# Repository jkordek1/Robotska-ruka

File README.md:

# Robotska-ruka
## What is it?
Board used for controlling multiple servo motors and their measurement of current.

WiFI capability via ESP32.

## Project status
Development stopped.

## Images

## Project folder structure
    .
    ├── ...
    ├── Images                  # Project images folder
    ├── Output files            # Gerber files folder
    ├── KiCad files             # Main folder
    ├── Schematic.pdf           # Schematic in .pdf format
    └── ...

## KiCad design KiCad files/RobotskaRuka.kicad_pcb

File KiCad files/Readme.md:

Board used for controlling multiple servo motors and current measurement of each motor.

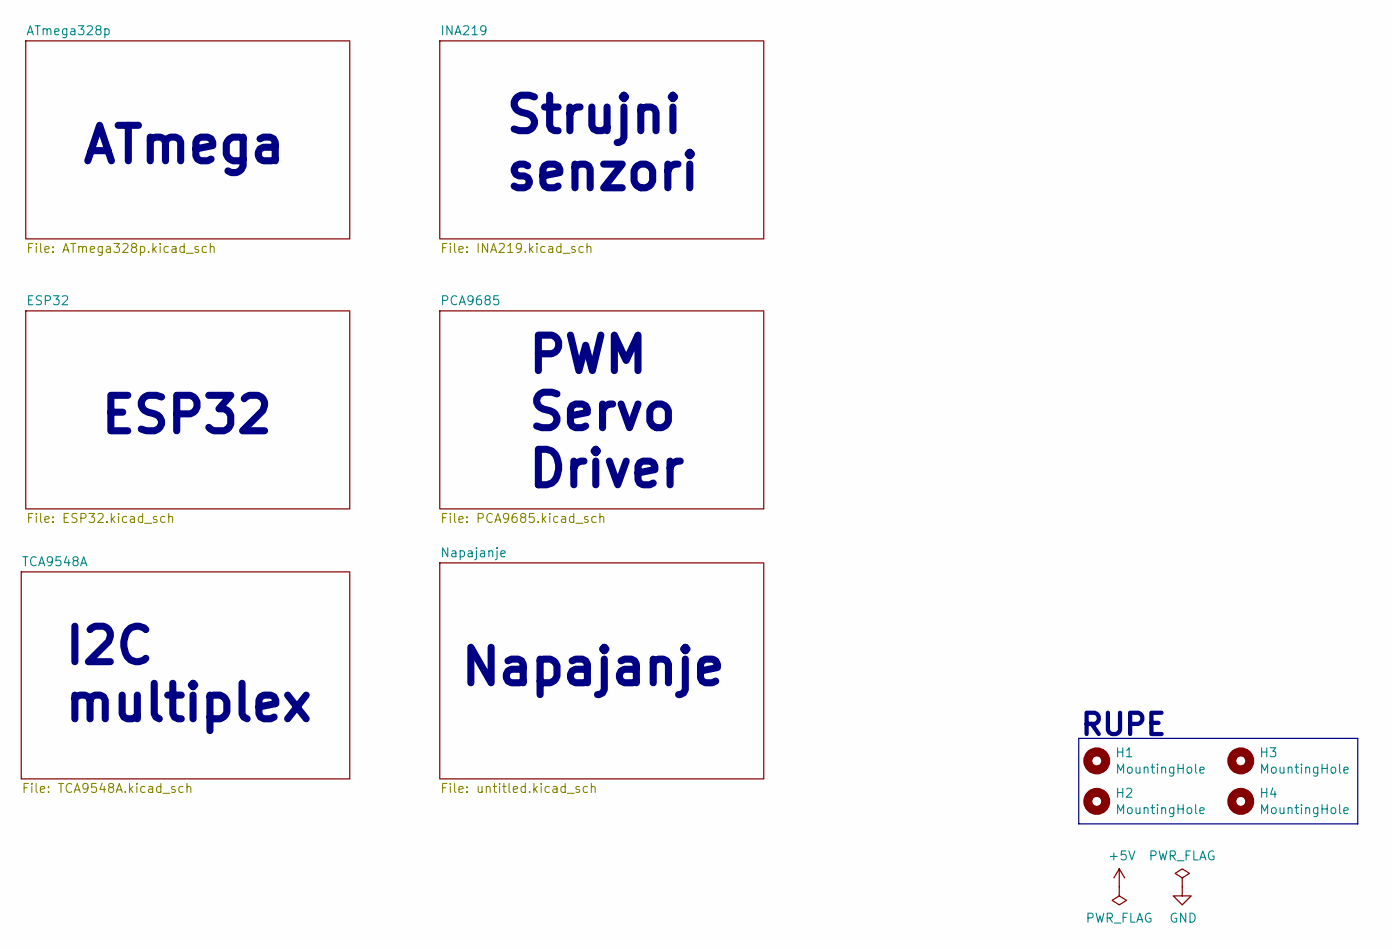
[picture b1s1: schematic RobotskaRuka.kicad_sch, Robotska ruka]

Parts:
H1, H2, H3, H4: MountingHole; MountingHole_3.2mm_M3_Pad_Via

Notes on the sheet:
ESP32
RUPE
Strujni senzori
PWM Servo Driver
Napajanje
ATmega
I2C multiplex

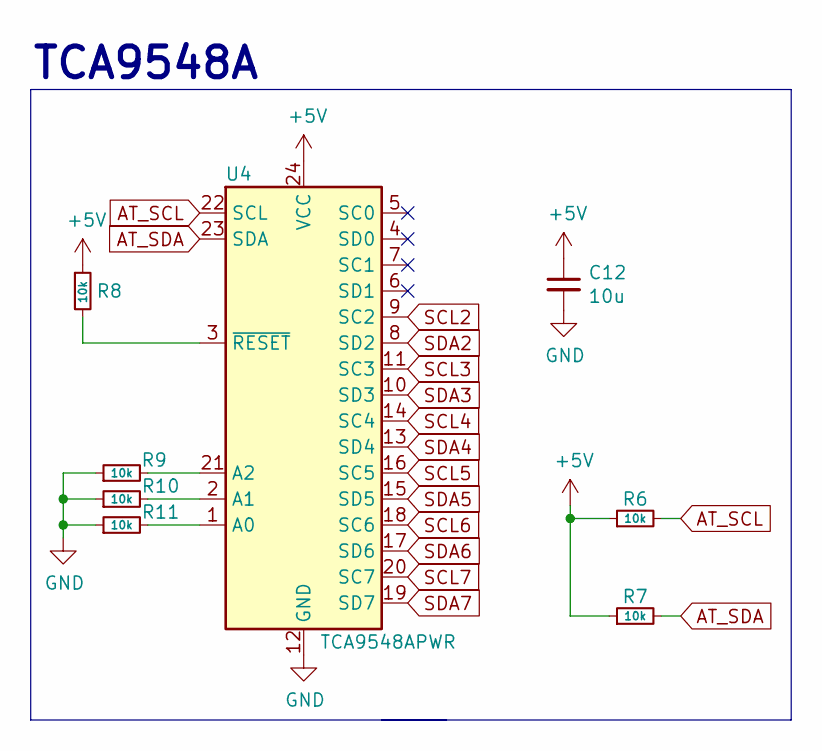
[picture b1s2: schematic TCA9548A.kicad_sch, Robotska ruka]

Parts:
C12: 10u; C_0805_2012Metric
R6, R7, R8, R9, R10, R11: 10k; R_0805_2012Metric
U4: TCA9548APWR; TSSOP-24_4.4x7.8mm_P0.65mm

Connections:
+5V: C12.1, R6.1, R7.1, R8.1, U4.24 (VCC); also elsewhere on the board
AT_SCL: R6.2, U4.22 (SCL); also elsewhere on the board
AT_SDA: R7.2, U4.23 (SDA); also elsewhere on the board
GND: C12.2, R9.1, R10.1, R11.1, U4.12 (GND); also elsewhere on the board
unnamed: R8.2, U4.3 (~RESET)
unnamed: R9.2, U4.21 (A2)
unnamed: R10.2, U4.2 (A1)
unnamed: R11.2, U4.1 (A0)
SCL1: U4.7 (SC1)
SCL2: U4.9 (SC2); also elsewhere on the board
SCL3: U4.11 (SC3); also elsewhere on the board
SCL4: U4.14 (SC4); also elsewhere on the board
SCL5: U4.16 (SC5); also elsewhere on the board
SCL6: U4.18 (SC6); also elsewhere on the board
SCL7: U4.20 (SC7); also elsewhere on the board
SDA1: U4.6 (SD1)
SDA2: U4.8 (SD2); also elsewhere on the board
SDA3: U4.10 (SD3); also elsewhere on the board
SDA4: U4.13 (SD4); also elsewhere on the board
SDA5: U4.15 (SD5); also elsewhere on the board
SDA6: U4.17 (SD6); also elsewhere on the board
SDA7: U4.19 (SD7); also elsewhere on the board

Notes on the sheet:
TCA9548A

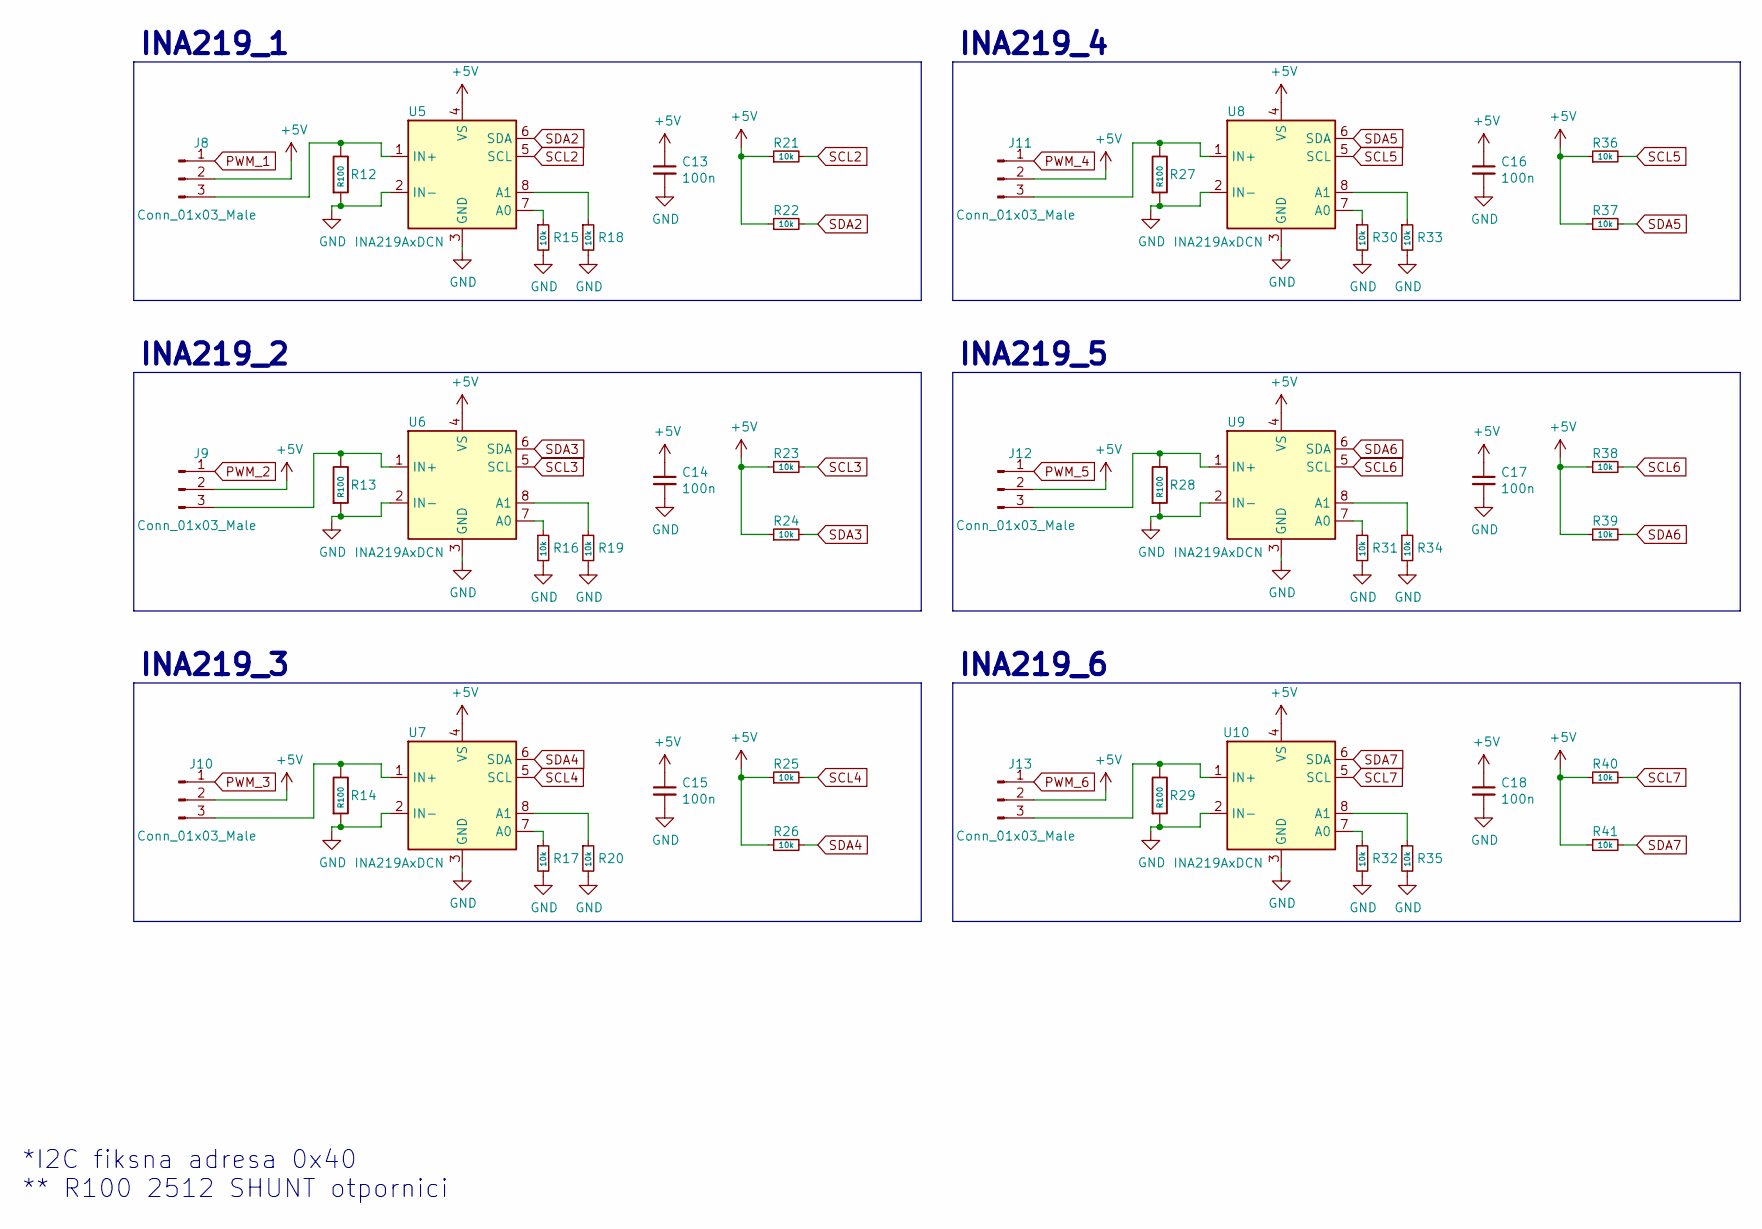
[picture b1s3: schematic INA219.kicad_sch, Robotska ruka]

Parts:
C13, C14, C15, C16, C17, C18: 100n; C_0805_2012Metric
J8, J9, J10, J11, J12, J13: Conn_01x03_Male; PinHeader_1x03_P2.54mm_Horizontal
R12, R13, R14, R27, R28, R29: R100; R_2512_6332Metric
R15, R16, R17, R18, R19, R20, R21, R22, R23, R24, R25, R26, R30, R31, R32, R33, R34, R35, R36, R37, R38, R39, R40, R41: 10k; R_0805_2012Metric
U5, U6, U7, U8, U9, U10: INA219AxDCN; SOT-23-8

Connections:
+5V: C13.1, C14.1, C15.1, C16.1, C17.1, C18.1, J8.2, J9.2, J10.2, J11.2, J12.2, J13.2, R21.1, R22.1, R23.1, R24.1, R25.1, R26.1, R36.1, R37.1, R38.1, R39.1, R40.1, R41.1, U5.4 (VS), U6.4 (VS), U7.4 (VS), U8.4 (VS), U9.4 (VS), U10.4 (VS); also elsewhere on the board
GND: C13.2, C14.2, C15.2, C16.2, C17.2, C18.2, R12.2, R13.2, R14.2, R15.2, R16.2, R17.2, R18.2, R19.2, R20.2, R27.2, R28.2, R29.2, R30.2, R31.2, R32.2, R33.2, R34.2, R35.2, U5.2 (IN-), U5.3 (GND), U6.2 (IN-), U6.3 (GND), U7.2 (IN-), U7.3 (GND), U8.2 (IN-), U8.3 (GND), U9.2 (IN-), U9.3 (GND), U10.2 (IN-), U10.3 (GND); also elsewhere on the board
unnamed: J8.3, R12.1, U5.1 (IN+)
unnamed: J9.3, R13.1, U6.1 (IN+)
unnamed: J10.3, R14.1, U7.1 (IN+)
unnamed: J11.3, R27.1, U8.1 (IN+)
unnamed: J12.3, R28.1, U9.1 (IN+)
unnamed: J13.3, R29.1, U10.1 (IN+)
unnamed: R15.1, U5.7 (A0)
unnamed: R16.1, U6.7 (A0)
unnamed: R17.1, U7.7 (A0)
unnamed: R18.1, U5.8 (A1)
unnamed: R19.1, U6.8 (A1)
unnamed: R20.1, U7.8 (A1)
unnamed: R30.1, U8.7 (A0)
unnamed: R31.1, U9.7 (A0)
unnamed: R32.1, U10.7 (A0)
unnamed: R33.1, U8.8 (A1)
unnamed: R34.1, U9.8 (A1)
unnamed: R35.1, U10.8 (A1)
PWM_1: J8.1; also elsewhere on the board
PWM_2: J9.1; also elsewhere on the board
PWM_3: J10.1; also elsewhere on the board
PWM_4: J11.1; also elsewhere on the board
PWM_5: J12.1; also elsewhere on the board
PWM_6: J13.1; also elsewhere on the board
SCL2: R21.2, U5.5 (SCL); also elsewhere on the board
SCL3: R23.2, U6.5 (SCL); also elsewhere on the board
SCL4: R25.2, U7.5 (SCL); also elsewhere on the board
SCL5: R36.2, U8.5 (SCL); also elsewhere on the board
SCL6: R38.2, U9.5 (SCL); also elsewhere on the board
SCL7: R40.2, U10.5 (SCL); also elsewhere on the board
SDA2: R22.2, U5.6 (SDA); also elsewhere on the board
SDA3: R24.2, U6.6 (SDA); also elsewhere on the board
SDA4: R26.2, U7.6 (SDA); also elsewhere on the board
SDA5: R37.2, U8.6 (SDA); also elsewhere on the board
SDA6: R39.2, U9.6 (SDA); also elsewhere on the board
SDA7: R41.2, U10.6 (SDA); also elsewhere on the board

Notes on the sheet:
INA219_1
INA219_5
*I2C fiksna adresa 0x40 ** R100 2512 SHUNT otpornici
INA219_2
INA219_6
INA219_4
INA219_3

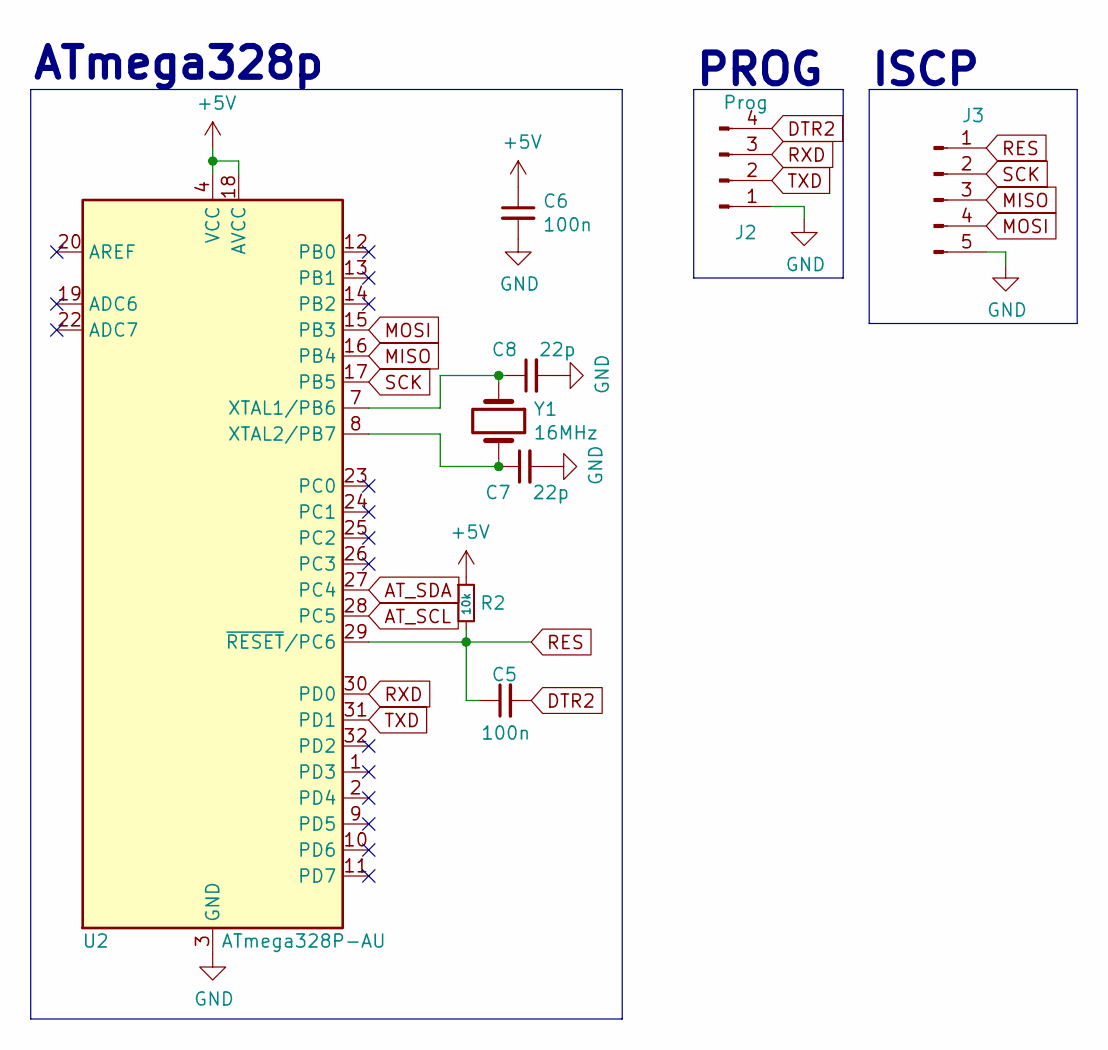
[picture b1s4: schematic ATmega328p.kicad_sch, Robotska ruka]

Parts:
C5, C6: 100n; C_0805_2012Metric
C7, C8: 22p; C_0805_2012Metric
J2: Prog; PinHeader_1x04_P2.54mm_Horizontal
J3: Conn_01x05_Male; PinHeader_1x05_P2.54mm_Horizontal
R2: 10k; R_0805_2012Metric
U2: ATmega328P-AU; TQFP-32_7x7mm_P0.8mm
Y1: 16MHz; Crystal_HC49-4H_Vertical

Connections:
+5V: C6.1, R2.1, U2.4 (VCC), U2.6 (VCC), U2.18 (AVCC); also elsewhere on the board
AT_SCL: U2.28 (PC5); also elsewhere on the board
AT_SDA: U2.27 (PC4); also elsewhere on the board
DTR2: C5.2, J2.4
GND: C6.2, C7.2, C8.2, J2.1, J3.5, U2.3 (GND), U2.5 (GND), U2.21 (GND); also elsewhere on the board
MISO: J3.3, U2.16 (PB4)
MOSI: J3.4, U2.15 (PB3)
unnamed: C7.1, U2.8 (XTAL2/PB7), Y1.2
unnamed: C8.1, U2.7 (XTAL1/PB6), Y1.1
RES: C5.1, J3.1, R2.2, U2.29 (~RESET/PC6)
RXD: J2.3, U2.30 (PD0); also elsewhere on the board
SCK: J3.2, U2.17 (PB5)
TXD: J2.2, U2.31 (PD1); also elsewhere on the board

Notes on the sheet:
ISCP
ATmega328p
PROG

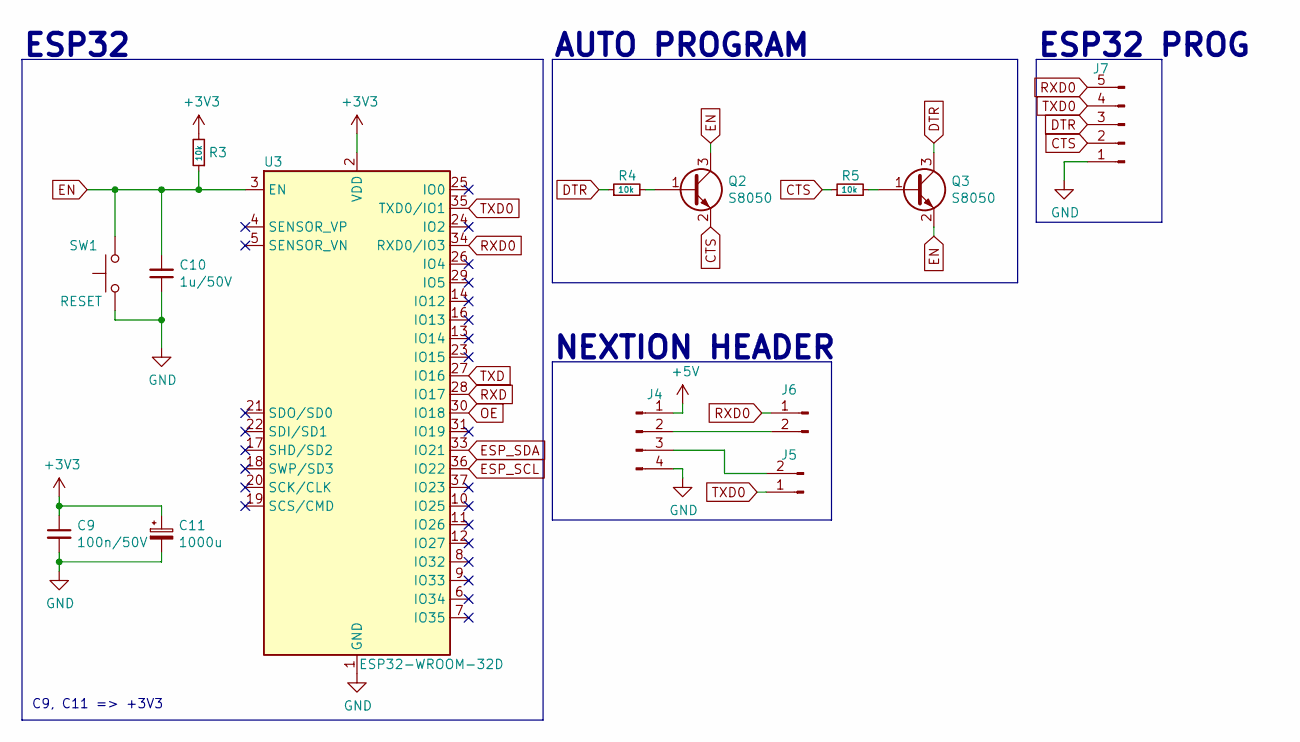
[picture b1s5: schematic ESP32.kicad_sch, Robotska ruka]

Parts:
C9: 100n/50V; C_0805_2012Metric; LCSC Part # C415304
C10: 1u/50V; C_0805_2012Metric; LCSC Part # C342759
C11: 1000u; CP_EIA-7343-31_Kemet-D; LCSC Part # C403807
J4: Conn_01x04; PinHeader_1x04_P2.54mm_Horizontal
J5, J6: Conn_01x02; PinHeader_1x02_P2.54mm_Horizontal
J7: Conn_01x05; PinHeader_1x05_P2.54mm_Horizontal
Q2, Q3: S8050; SOT-23; LCSC Part # C380921
R3, R4, R5: 10k; R_0805_2012Metric; LCSC Part # C100047
SW1: RESET; SW_Tactile_SPST_Angled_PTS645Vx39-2LFS; LCSC Part # C285519
U3: ESP32-WROOM-32D; ESP32-WROOM-32; LCSC Part # C473012

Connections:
+3V3: C9.1, C11.1, R3.2, U3.2 (VDD); also elsewhere on the board
+5V: J4.1; also elsewhere on the board
CTS: J7.2, Q2.2 (E), R5.1
DTR: J7.3, Q3.3 (C), R4.1
EN: C10.2, Q2.3 (C), Q3.2 (E), R3.1, SW1.2, U3.3 (EN)
ESP_SCL: U3.36 (IO22); also elsewhere on the board
ESP_SDA: U3.33 (IO21); also elsewhere on the board
GND: C9.2, C10.1, C11.2, J4.4, J7.1, SW1.1, U3.1 (GND), U3.15 (GND), U3.38 (GND), U3.39 (GND); also elsewhere on the board
unnamed: J4.2, J6.2
unnamed: J4.3, J5.2
unnamed: Q2.1 (B), R4.2
unnamed: Q3.1 (B), R5.2
OE: U3.30 (IO18); also elsewhere on the board
RXD: U3.28 (IO17); also elsewhere on the board
RXD0: J6.1, J7.5, U3.34 (RXD0/IO3)
TXD: U3.27 (IO16); also elsewhere on the board
TXD0: J5.1, J7.4, U3.35 (TXD0/IO1)

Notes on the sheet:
C9, C11 => +3V3
ESP32 PROG
ESP32
NEXTION HEADER
AUTO PROGRAM

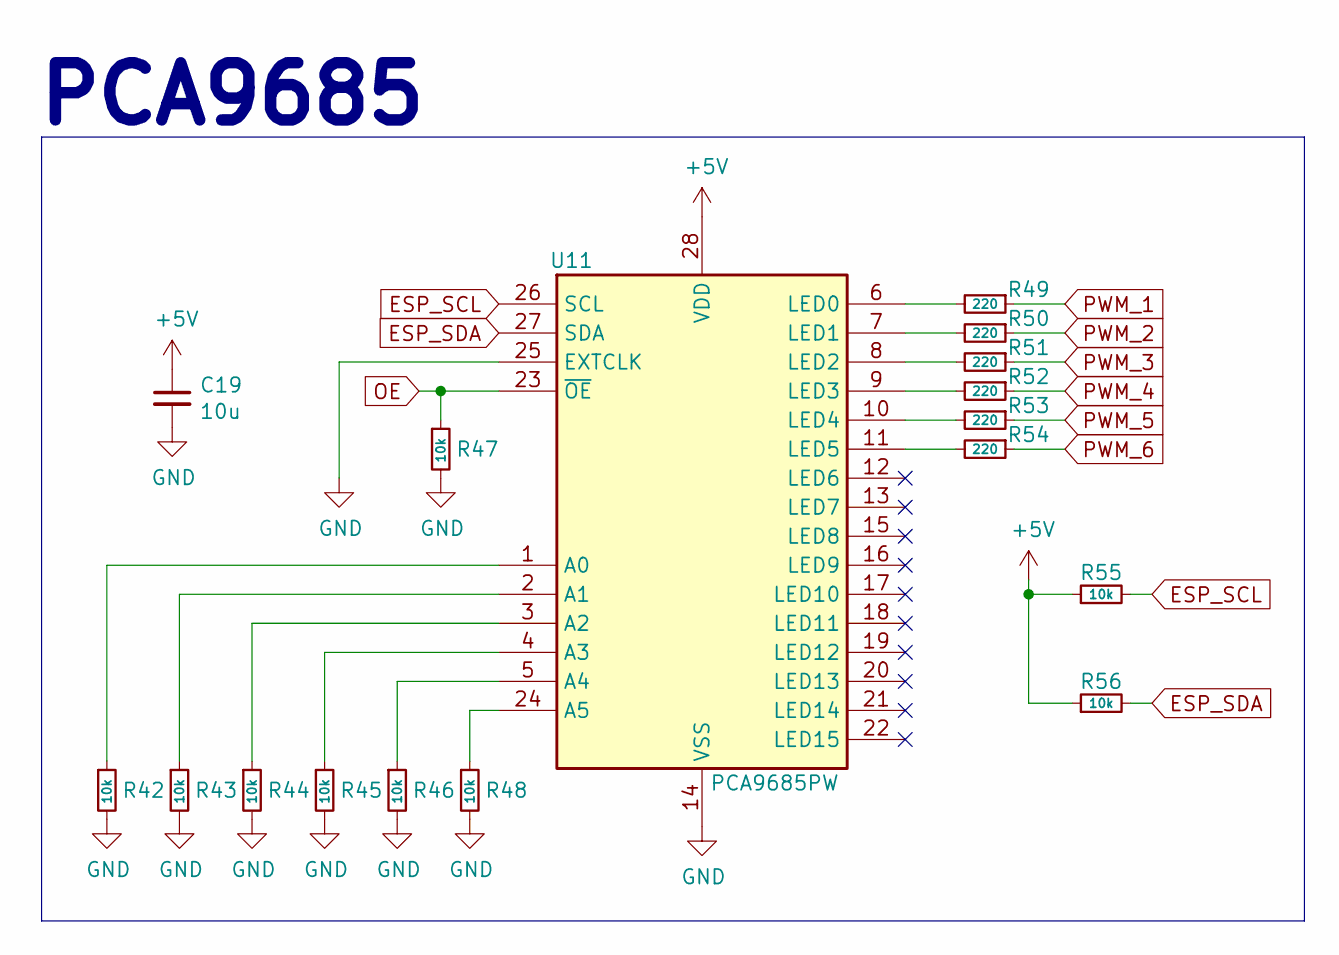
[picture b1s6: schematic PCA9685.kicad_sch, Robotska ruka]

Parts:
C19: 10u; C_0805_2012Metric
R42, R43, R44, R45, R46, R47, R48, R55, R56: 10k; R_0805_2012Metric
R49, R50, R51, R52, R53, R54: 220; R_0805_2012Metric
U11: PCA9685PW; TSSOP-28_4.4x9.7mm_P0.65mm

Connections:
+5V: C19.1, R55.1, R56.1, U11.28 (VDD); also elsewhere on the board
ESP_SCL: R55.2, U11.26 (SCL); also elsewhere on the board
ESP_SDA: R56.2, U11.27 (SDA); also elsewhere on the board
GND: C19.2, R42.2, R43.2, R44.2, R45.2, R46.2, R47.2, R48.2, U11.14 (VSS), U11.25 (EXTCLK); also elsewhere on the board
unnamed: R42.1, U11.1 (A0)
unnamed: R43.1, U11.2 (A1)
unnamed: R44.1, U11.3 (A2)
unnamed: R45.1, U11.4 (A3)
unnamed: R46.1, U11.5 (A4)
unnamed: R48.1, U11.24 (A5)
unnamed: R49.2, U11.6 (LED0)
unnamed: R50.2, U11.7 (LED1)
unnamed: R51.2, U11.8 (LED2)
unnamed: R52.2, U11.9 (LED3)
unnamed: R53.2, U11.10 (LED4)
unnamed: R54.2, U11.11 (LED5)
OE: R47.1, U11.23 (~OE); also elsewhere on the board
PWM_1: R49.1; also elsewhere on the board
PWM_2: R50.1; also elsewhere on the board
PWM_3: R51.1; also elsewhere on the board
PWM_4: R52.1; also elsewhere on the board
PWM_5: R53.1; also elsewhere on the board
PWM_6: R54.1; also elsewhere on the board

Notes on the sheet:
PCA9685

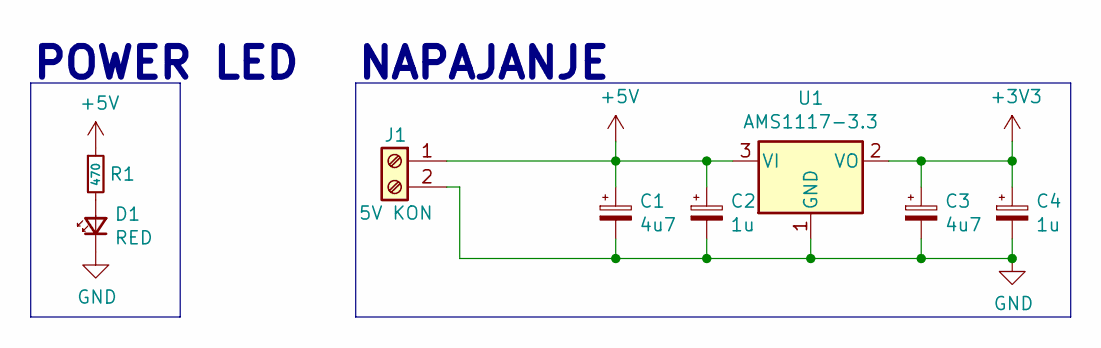
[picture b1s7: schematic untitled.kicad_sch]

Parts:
C1, C3: 4u7; CP_Elec_4x5.4
C2, C4: 1u; C_0805_2012Metric
D1: RED; LED_0805_2012Metric
J1: 5V KON; TerminalBlock_Phoenix_MKDS-1,5-2-5.08_1x02_P5.08mm_Horizont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
R1: 470; R_0805_2012Metric
U1: AMS1117-3.3; SOT-223-3_TabPin2

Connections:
+3V3: C3.1, C4.1, U1.2 (VO); also elsewhere on the board
+5V: C1.1, C2.1, J1.1, R1.1, U1.3 (VI); also elsewhere on the board
GND: C1.2, C2.2, C3.2, C4.2, D1.1 (K), J1.2, U1.1 (GND); also elsewhere on the board
unnamed: D1.2 (A), R1.2

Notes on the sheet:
POWER LED
NAPAJANJE

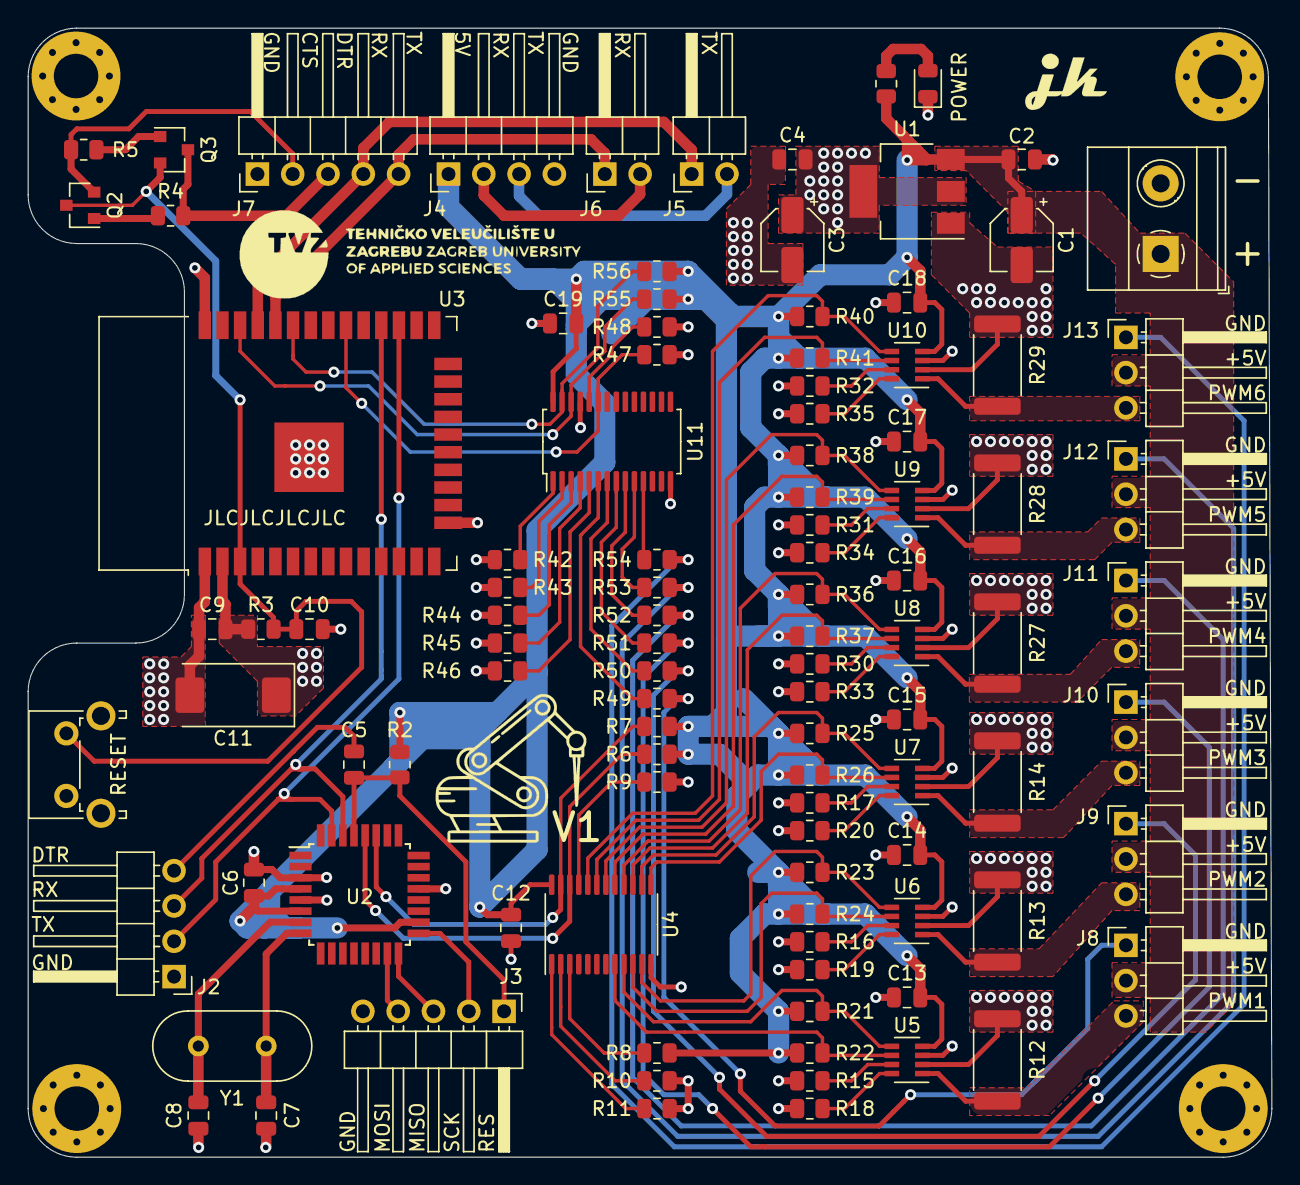
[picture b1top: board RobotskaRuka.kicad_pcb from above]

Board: 2 copper layers, 89.5 x 81.2 mm, 108 parts (0 on the bottom side), 79 nets.

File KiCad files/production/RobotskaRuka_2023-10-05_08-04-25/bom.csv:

Designator,Footprint,Quantity,Value,LCSC Part #
"C1, C3",CP_Elec_4x5.4,2,4u7,
C10,0805,1,1u/50V,C342759
C11,CP_EIA-7343-31_Kemet-D,1,1000u,C403807
"C12, C19",0805,2,10u,
"C13, C14, C15, C16, C17, C18, C5, C6",0805,8,100n,
"C2, C4",0805,2,1u,
"C7, C8",0805,2,22p,
C9,0805,1,100n/50V,C415304
D1,0805,1,RED,
"H1, H2, H3, H4",MountingHole_3.2mm_M3_Pad_Via,4,MountingHole,
J1,"TerminalBlock_Phoenix_MKDS-1,5-2-5.08_1x02_P5.08mm_Horizontal",1,5V KON,
"J10, J11, J12, J13, J8, J9",PinHeader_1x03_P2.54mm_Horizontal,6,Conn_01x03_Male,
J2,PinHeader_1x04_P2.54mm_Horizontal,1,Prog,
J3,PinHeader_1x05_P2.54mm_Horizontal,1,Conn_01x05_Male,
J4,PinHeader_1x04_P2.54mm_Horizontal,1,Conn_01x04,
"J5, J6",PinHeader_1x02_P2.54mm_Horizontal,2,Conn_01x02,
J7,PinHeader_1x05_P2.54mm_Horizontal,1,Conn_01x05,
"Q2, Q3",SOT-23,2,S8050,C380921
R1,0805,1,470,
"R10, R11, R15, R16, R17, R18, R19, R2, R20, R21, R22, R23, R24, R25, R26, R30, R31, R32, R33, R34, R35, R36, R37, R38, R39, R40, R41, R42, R43, R44, R45, R46, R47, R48, R55, R56, R6, R7, R8, R9",0805,40,10k,
"R12, R13, R14, R27, R28, R29",2512,6,R100,
"R3, R4, R5",0805,3,10k,C100047
"R49, R50, R51, R52, R53, R54",0805,6,220,
SW1,SW_Tactile_SPST_Angled_PTS645Vx39-2LFS,1,RESET,C285519
U1,SOT-223-3_TabPin2,1,AMS1117-3.3,
"U10, U5, U6, U7, U8, U9",SOT-23-8,6,INA219AxDCN,
U11,TSSOP-28_4.4x9.7mm_P0.65mm,1,PCA9685PW,
U2,TQFP-32_7x7mm_P0.8mm,1,ATmega328P-AU,
U3,ESP32-WROOM-32,1,ESP32-WROOM-32D,C473012
U4,TSSOP-24_4.4x7.8mm_P0.65mm,1,TCA9548APWR,
Y1,Crystal_HC49-4H_Vertical,1,16MHz,

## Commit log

2022-02-09 First
2022-02-09 update folders
2022-02-09 image
2022-02-09 output
